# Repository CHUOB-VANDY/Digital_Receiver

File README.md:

# Digital_Receiver
Wireless receiver based on AS01-SPIPX (NRF)

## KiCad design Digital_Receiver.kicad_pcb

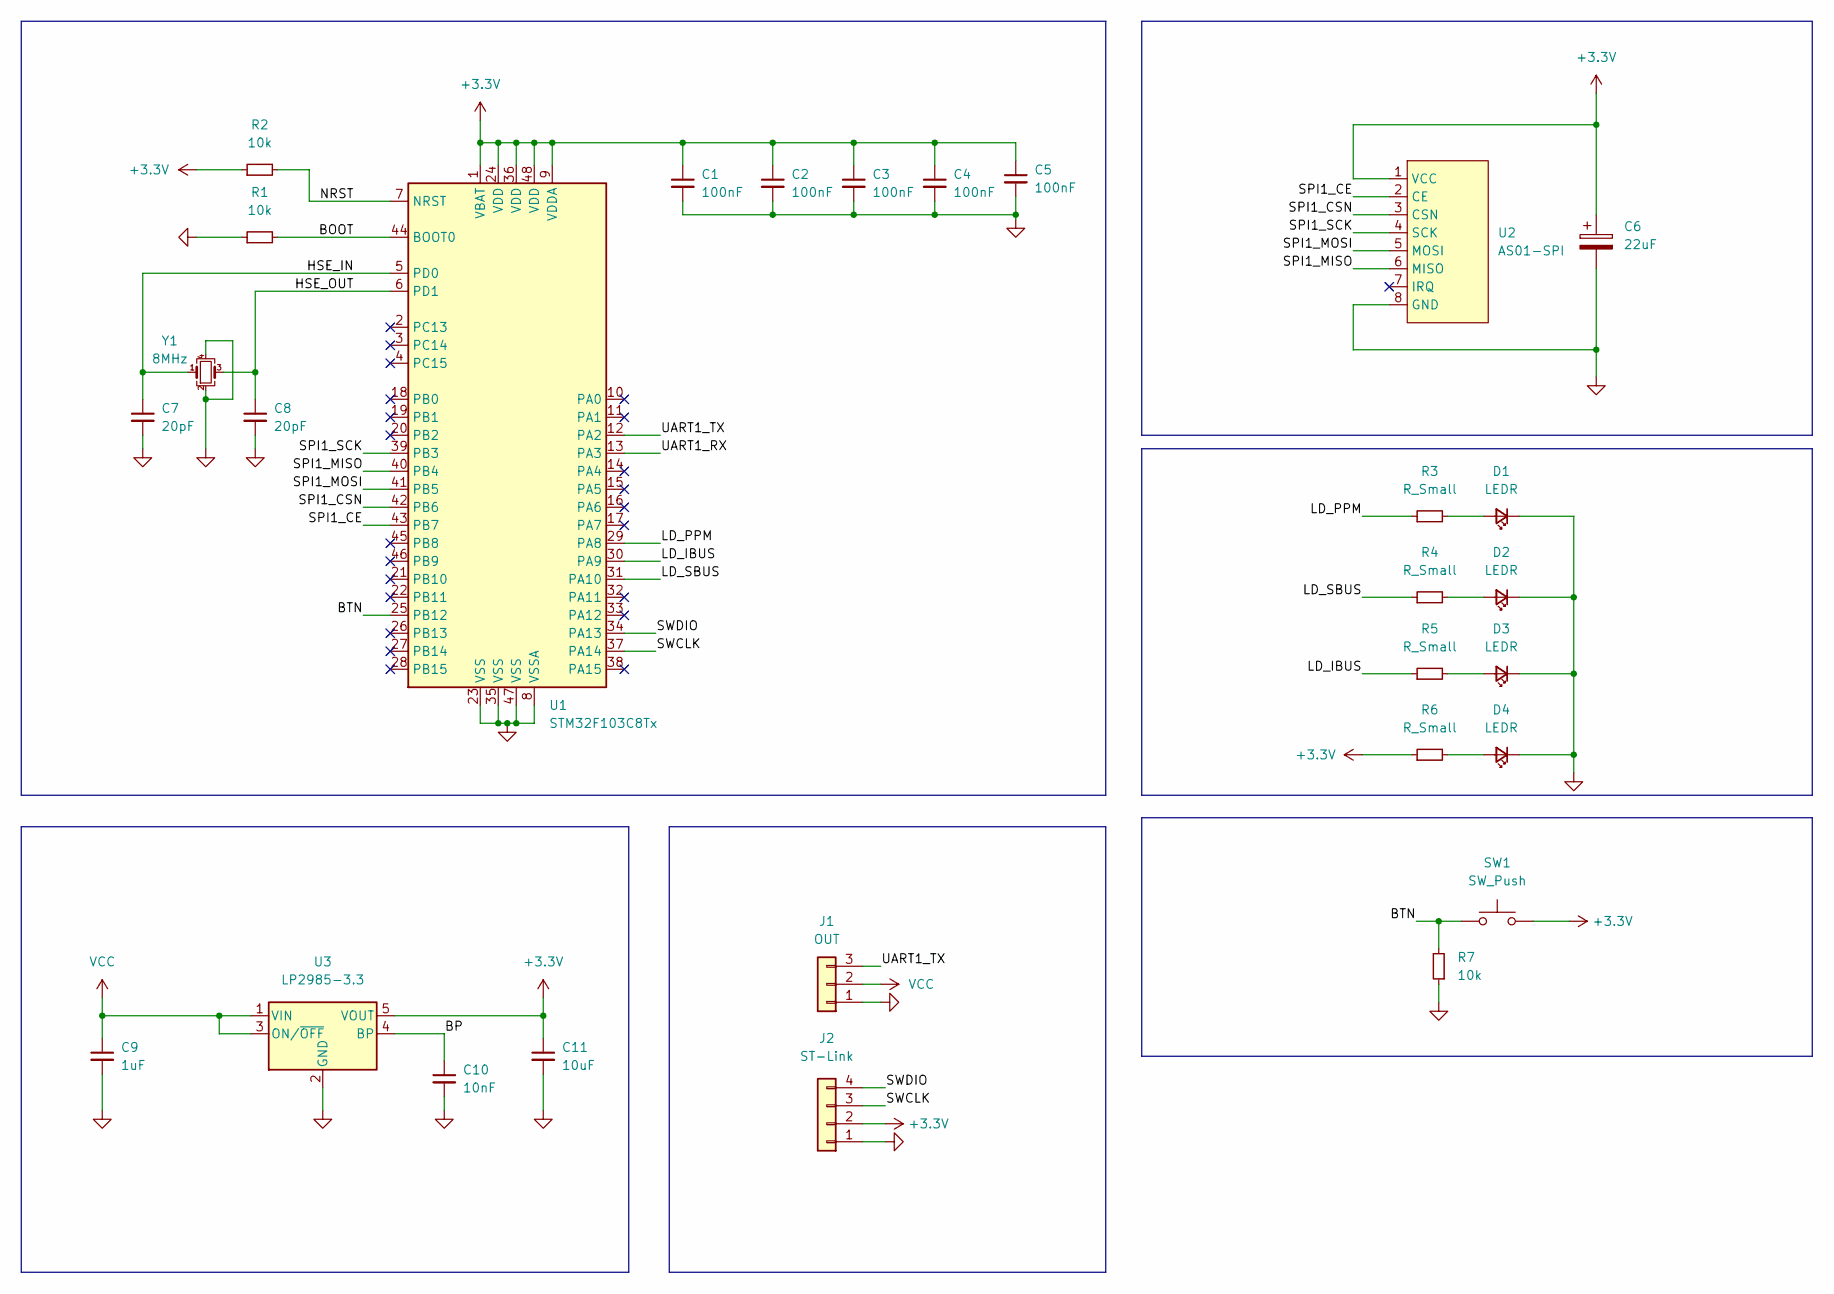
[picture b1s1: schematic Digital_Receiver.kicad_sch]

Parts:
C1, C2, C3, C4, C5: 100nF; C_0603_1608Metric
C6: 22uF; CP_EIA-3216-10_Kemet-I
C7, C8: 20pF; C_0603_1608Metric
C9: 1uF; C_0603_1608Metric
C10: 10nF; C_0603_1608Metric
C11: 10uF; C_0805_2012Metric
D1, D2, D3, D4: LEDR; LED_0603_1608Metric
J1: OUT; PinHeader_1x03_P2.54mm_Horizontal
J2: ST-Link; ConPadx04-1.5mm
R1, R2, R7: 10k; R_0603_1608Metric
R3, R4, R5, R6: R_Small; R_0603_1608Metric
SW1: SW_Push; Panasonic_EVQPUM_EVQPUD
U1: STM32F103C8Tx; LQFP-48_7x7mm_P0.5mm
U2: AS01-SPI
U3: LP2985-3.3; SOT-23-5
Y1: 8MHz; Crystal_SMD_3225-4Pin_3.2x2.5mm

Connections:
+3V3: C1.1, C2.1, C3.1, C4.1, C5.1, C6.1, C11.1, J2.2, R2.1, R6.1, SW1.2, U1.1 (VBAT), U1.9 (VDDA), U1.24 (VDD), U1.36 (VDD), U1.48 (VDD), U2.1 (VCC), U3.5 (VOUT)
/BOOT: R1.2, U1.44 (BOOT0)
/BP: C10.1, U3.4 (BP)
/BTN: R7.2, SW1.1, U1.25 (PB12)
/HSE_IN: C7.1, U1.5 (PD0), Y1.1
/HSE_OUT: C8.1, U1.6 (PD1), Y1.3
/LD_IBUS: R5.1, U1.30 (PA9)
/LD_PPM: R3.1, U1.29 (PA8)
/LD_SBUS: R4.1, U1.31 (PA10)
/NRST: R2.2, U1.7 (NRST)
/SPI1_CE: U1.43 (PB7), U2.2 (CE)
/SPI1_CSN: U1.42 (PB6), U2.3 (CSN)
/SPI1_MISO: U1.40 (PB4), U2.6 (MISO)
/SPI1_MOSI: U1.41 (PB5), U2.5 (MOSI)
/SPI1_SCK: U1.39 (PB3), U2.4 (SCK)
/SWCLK: J2.3, U1.37 (PA14)
/SWDIO: J2.4, U1.34 (PA13)
/UART1_RX: U1.13 (PA3)
/UART1_TX: J1.3, U1.12 (PA2)
GND: C1.2, C2.2, C3.2, C4.2, C5.2, C6.2, C7.2, C8.2, C9.2, C10.2, C11.2, D1.1 (K), D2.1 (K), D3.1 (K), D4.1 (K), J1.1, J2.1, R1.1, R7.1, U1.8 (VSSA), U1.23 (VSS), U1.35 (VSS), U1.47 (VSS), U2.8 (GND), U3.2 (GND), Y1.2, Y1.4
unnamed: D2.2 (A), R4.2
unnamed: D1.2 (A), R3.2
unnamed: D3.2 (A), R5.2
unnamed: D4.2 (A), R6.2
VCC: C9.1, J1.2, U3.1 (VIN), U3.3 (ON/~OFF)

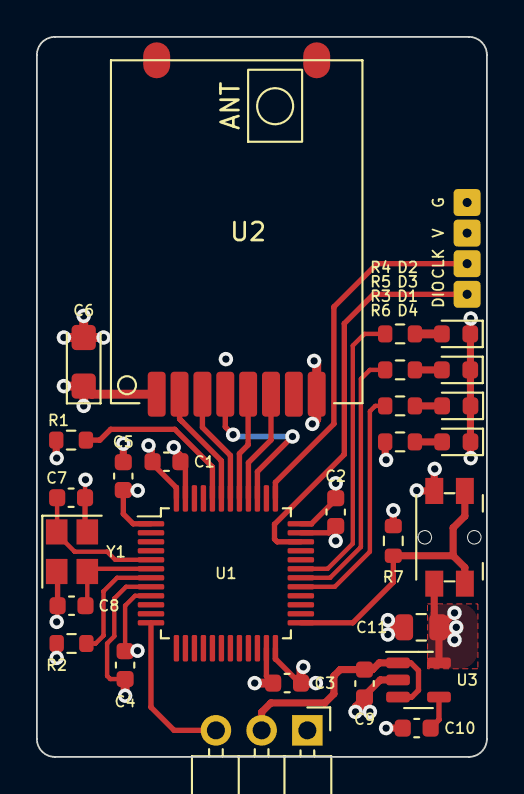
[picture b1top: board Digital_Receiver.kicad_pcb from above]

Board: 4 copper layers, 25.0 x 40.0 mm, 29 parts (0 on the bottom side), 24 nets.
